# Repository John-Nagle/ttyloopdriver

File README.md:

# ttyloopdriver
Hardware device for driving antique Teletype machines.

For use with 60mA current loop Teletypes at 45 baud.

## Status 

Version 3.3 works, successfully driving a Model 15
Teletype. It's also been built by Steve Garrison and
used to drive a Model 28 Teletype.

# What it is

This is a board to allow connecting antique Teletype machines to a computer through
a USB port. It's for Teletype Model 14 and 15 machines, which use 60mA current
loops.   This board needs no external power supply other than the USB port.
This approach uses only about 1 watt of power, drawing 200mA from the USB port. 

# How it works

The Teletype needs a current of 60mA and an initial voltage of 120V to operate the
selector magnet. The 120V is needed to overcome the huge inductance of the selector
magnet; once the magnet is charged, the required voltage is only a few volts. So the
circuit charges up some capacitors and dumps them into the selector magnet at the start
of each 1 bit (called "MARK" in the Teletype world). After a few milliseconds, a
low-voltage sustain supply takes over to maintain the 60mA current. 

All this is powered entirely from a USB port. So there's a custom switching power
supply.

## Output to the Teletype

At the USB end is a CP2012 breakout board U3.  The Silicon Labs CP2102 is a USB
to serial converter, one of the few which can be reprogrammed for 45 baud
operation.  We reprogram it to map a request for 600 baud to 45 baud.
We also reprogram it to request 400mA from the USB port.

There are two power supplies for the output. One is a custom switching
power supply which, during SPACE, charges up a pair of 1uF ceramic capacitors C1 and C2 to
120V.  There's a board position for a C3 capacitor as well, in parallel with C1 and C2,
but this has not been necessary. These are through-hole components because very large SMT capacitors have capactance
which declines with voltage, which is unacceptable here. They're ceramics for low internal
resistance. 

These caps provide the initial power to pull in the selector magnet,
pushing 60mA through the huge (measured) at 5.5H inductance of the magnet coils.
The other is a 15V supply U8 which provides sustaining current at 60mA
once C2 and C11 have discharged.  Both power supplies feed, through diode D6,
a solid-state relay U4. The relay is controlled by the transmit
data line TxD from U3.

The switching power supply is controlled by an LT3750 capacitor charging
controller. This is the right tool for the job, but with pin spacing of 0.5mm,
is hard to solder. The LT3750 uses comparators and flip-flops to control
charging. 

The switcher is an isolated boost supply, consisting of
U1, T1, C1, C2, and some passives.  The controller signal GATE
turns the FET in Q1 on and off. Turning Q1 off produces an inductive
kick in T1, which has a 1:10 turns ratio.  This can produce
over 120VDC, which is used to charge C1 and C2.

Charging occurs only during SPACE. During MARK, TxD goes high,
inverter U9 inverts that signal, and so, on a MARK to SPACE
transition, the CHARGE input of U1 sees an edge which starts the
charging process.

When the charging process starts, a flip-flop inside U1 turns
on, and this turns on the GATE signal to Q1. This allows current
to flow through T1. The current ramps up linearly as the inductor
charges. Resistor R3, which is only 0.091 ohm, is used as a current
sense resistor to tell U1 when to shut off GATE, stopping current
though the transformer primary.  The value of R3 controls the maximum
current the charger will draw.

Then the transformer, disconnected from power, dumps its magnetic field
into the secondary, charging C1 and C2 through D1. As this happens, the
voltage across the transformer primary drops, and this is sensed via the
RDCM pin of U1. When that voltage difference is near zero, a comparator
in U1 turns the flip-flop back on, turning on GATE and starting the
cycle again. That's the oscillator in this.

There's also circuitry in U1 which senses the peak voltage level to which 
the primary of U1 rises during each charge cycle via RVout. This
is used to stop charging once the desired voltage has been reached.
It takes about 14ms to charge C1 and C2 to 120V, and then the 
charging stops.  The value of R4 controls this goal.
 
The sustain supply U8 is always on, but there is no load on it
during SPACE, because U4 is turned off.  So the two power
supplies take turns drawing
power from the USB port, which keeps the peak current down.

To allow this circuit to support various selector magnet resistances,
there's a linear current regulator at the end, consisting of Q2 and R5.
Q2 is a depletion-mode MOSFET, an unusual component useful for current
regulation over a wide voltage range. This limits the output current to
60mA. When driving a 220 ohm selector, this circuit isn't doing much
current limiting, but when driving a 55 ohm selector, it is. It also
provides short circuit protection, limiting short circuit current to
60mA. (A previous version of the board had a removable jumper for
adjusting the output current, but that was too 1980s. Now it's fully
automatic.)

## Input from the keyboard

On the keyboard side, U6, a very small 5V to 24V DC-DC
converter, produces enough voltage for Teletype keyboard
contacts, which may have oil or dirt on them.  A 5V
logic level is known to be too weak for this.  Another
opto-isolator, U5, isolates the keyboard from the logic
level circuitry.  There's a BREAK button, SW2, so that
a BREAK can be sent even if no keyboard is present.

## Motor control

A standard 5V solid state relay, such as a Crydom CSW2410-10 can 
be plugged into jack J3 for Teletype motor control.  This will
turn on when the USB serial port raises Request to Send and power is on.
The middle green light of D13 will also turn on.
The "Baudotrss" software package supports this function.

## Power management

This board is powered entirely from a USB port.  There are
strict rules about drawing power from a USB port, and most
modern laptop computers have a USB port controller wihich strictly
enforces them.  If a device draws too much current, even for a 
millisecond, the port turns off power, and usually won't
turn back on again until the laptop is turned off.  Devices
must negotiate with the power source for how much power they
want, and the power source can say no.  This happens when the
device is plugged into the USB port, or when the laptop turns
the port on.

USB devices are guaranteed 100mA, but if you want 
more than that, you have to ask. We ask for 400mA, below the 500mA  maximum
for USB versions 1 and 2, by programming a register in the CP2102
USB interface. We also set the speed for the serial port to 45 baud 
when 600 baud is requested. Programming is done with Silicon Labs' Simplicity Studio
program. 

If the host device says yes to the request for 400mA, the
CP2012 turns on /SUSPEND after successful completion of the
power handshake.  Turning off the device in software (as when
the host computer goes to sleep) will turn off /SUSPEND.

U2 is a AP2553W6 power control IC intended for USB ports.  When
/SUSPEND goes high, it turns on and lets power into the rest of
the board.  It also has a built-in power limit, set to 400mA by
resistor R16, which limits the inrush current as C1 charges at power
up.  If turn-on is successful, and SW1 is on, the VPWR line comes
up and everything on the board gets power, including the top
LED of D13. 

With some operating systems, this won't happen until
the USB port is opened by software.  If the computer goes to sleep,
everything will turn off.  Most USB hubs and some "smart" USB
extension cables will reject a request for 500mA, and the
light won't come on. If the light will come on when the USB cable
is directly plugged into a computer, but won't come on when plugged
in through a long cable or hub, that's the reason.

## Circuit protection

R1 and C3 are a filter for the inductive spikes from
the Teletype selector magnet. The back to back 120V Zeners
D10 and D11 protect against the inductive kickback spikes
from the selector magnet.

On the input side, C8, C12, and L3 keep the inductive
kickback from T1 from getting back into the USB power supply.

The AP2553W6 provides overload protection to the USB port.
It first acts as a current limiter, and if the overload continues,
it heats up, detects the overtemp condition, and cuts power.
The CPC1510G solid state relays also provide current limiting,
in case the printer output is shorted. A dead short across the
output will not damage anything. 

On the Teletype side, everything is isolated from ground and from the USB side.

## Test points

- W1 - low-voltage ground
- W2 - low-voltage power (4.5-5V to W1 GND when powered up)
- W3 - Low side of transformer primary. Watch the switcher action here.
- W4 - High side of switcher current sense resistor
- W5 - high-voltage ground
- W6 - high-voltage high side

## Connectors

J1 is the 1/4" Teletype printer jack, supplying 120VDC at 60mA for a Teletype Model
14 or 15.  Only one printer can be driven; there is not enoug power to drive a whole chain
of machines.

J2 is the 1/4" Teletype keyboard jack, supplying power for a Model 14/15 keyboard.
If nothing is plugged in, the jack shorts and the BREAK button still works.

P2 is a connection for a current meter.  A 100mA meter
is suggested. If a meter is not used, this plug must
be jumpered.

J3 is a smalll jack for a solid state relay (5V in) to
turn on the Teletype motor.  Use of this is optional.

## Controls and indicators

SW1 is the main power switch.

SW2 is a BREAK button, interrupting the keyboard circuit.  This works even if no keyboard is present.

D13 is a 3-high set of green LEDs.

 Bottom - Power ON
 
 Middle - Motor ON
 
 Top - Data output
 
## Computer interface

This unit appears to most computers as a serial port. No special driver should be required.
The port should be opened and set to 600 baud to request
45 baud output.  (The CP2102 must be programmed for this, because many systems can't request 45 baud. 600 baud is used
because that speed was never used for any historical devices.)  When power is on,
Data Set Ready will turn on. When power is on and the motor is running, Clear to Send will turn on.
Power management works; if the computer goes to sleep or suspends, the board will turn off.

## Firmware

The USB to serial converter part on the board must be configured to output 45 baud. See the README file in the
"firmware" directory for instructions.  The driving software must request 600 baud to get 45 baud, because 45
baud is no longer a standard baud rate.

## Fabricating the PC board

Standard Gerber and drill files are in "board/fab/fab.zip".  These are known to work with Seeed Studio
in Shentzen, and should work with other board shops.

## Packaging

The board is 75mm x 120mm, and will fit in a Hammond 1455K1202 box. Patterns for cutting the end plates for the box
are in the directory "case".  The Corel Draw files will work with Epilog laser cutters. We use 1/16" black  acrylic.

## Bill of materials

The bill of materials is in "board/ttydriver01.xml", in KiCAD format.  If this file is run through the Python program
in "tools/src/kicadbomtovendor.py", CSV files are generated. From the command line, when in the directory "board", try

    python3 ../tools/src/kicadbomtovendor ttydriver01.xml --split=VENDOR
    
This will generate CSV files for Digikey, Robotshop, and Coilcraft. The Digikey CSV file can be read by most spreadsheet
programs, and can be fed into the Digikey BOM system, which will look up and price all the parts. Various parts may be out
of stock, but every part on that list has been shipped to us from DigiKey at least once. Substitute out of stock resistors
and caps with equivalent parts if needed.

## Assembly hints

### CP2102 board mounting.

Mount the CP2102 board to the main board without sockets using pin headers.  If you mount it with a socket,
the board won't fit in the box. The CP2102 board comes with angled headers soldered on. Those have to be 
removed.  Solder straight 0.10 inch headers soldered into all the connector holes on the CP2102 board.
The CP2102 board comes with the needed header pins.

### Part substitution

The manufacturer isn't critical.  None of the resistors
are doing anything exotic. R3, R5, and R16 are 1% for a reason;
they're all for current sensing.  The others aren't critical and 5% resistors will work.

#### Obsolete parts
As of March 2021, the SiLabs CP2102 USB to serial part is "not recommended for new designs".
The "drop in replacement" CP2012N **will not work.** It will not run at speeds below 300 baud.

From [SiLabs' porting guide](https://www.silabs.com/documents/public/application-notes/an976-cp2102-3-4-9-to-cp2102n-porting-guide.pdf): 
*"Baud Rate Aliasing is a feature that allows a device to use a pre-defined baud rate in place of a baud rate that is requested by the user.
For example, a device using Baud Rate Aliasing can be programmed to use a baud rate of 45 bps whenever 300 bps is requested.
Baud Rate Aliasing is not supported on the CP2102N.
If Baud Rate Aliasing is used in a CP2102/9 design, the CP2102N is incompatible as a replacement."*

It's become difficult to find serial devices that will run at 45 baud.

### Compatibiilty with Teletype model 15 machines with noise suppression capacitors.
Some Model 15 teletypes have an RF noise suppression capacitor across the keyboard.
The capacitor used is large enough to cause typing errors with this board, because the keyboard circuit doesn't draw
enough power to discharge the capacitor. It may be necessary to disconnect the noise suppression option.

### Soldering

This board has been assembled by using solder paste for the surface mount
parts, placing the parts, then reflowing in a reflow oven. It's a straightforward
job by modern SMT standards. This will require SMT skills and tools. 
U1 has 0.5mm pin spacing, which is tight. 

Check for solder bridges, especially between pins of U1. The pads of U1 are laid out so that 
solder bridges tend to occur near the ends of the pins, where you can
get at them with copper braid and a pointed soldering iron tip.

### Initial testing

#### 1. Plug into a computer with a USB port.

No software required yet.  See that the
computer recognizes it as a USB device.

#### 2. Power check

W1 is ground, W2 is Vcc. Should see
4.8V between those two with the power
switch on.  Bottom green light should
turn on. This may not happen unless some
program has the USB port open, which turns
it on.

#### 3. Reprogram CP2102

If you haven't reprogrammed the
SiLabs baord for 45 baud, do so now.

#### 4. Send data

Send data from Baudotrss or Heavy
Metal at 45 baud. Watch the lights on the
serial board blink.  Top green light should
blink.

#### 5. Check high voltage.

W5 is HV ground. W6 is the high side of
the capacitors.  Expect to see 120V there
with no load on the output.  You have to
send some data to get a voltage there,
because the switcher only charges the
cap after a MARK to SPACE transition.
R14 will discharge the caps in a few
seconds, so after power-off it doesn't
retain high voltage. So you need data
to keep high voltage.

#### 6. Check current

With no data being sent but with something
driving the port, hook up a current meter
to the printer jack.  Should register 60mA,
even into a dead short. The current limiter
can handle this. Q2 will heat up, but it's
rated for 150C and it only heats up to 80C or so
driving a dead short for 20 minutes.

#### 7. Connect a Teletype and send data

If all those tests work, you're probably good
to run a Teletype.  Enjoy!

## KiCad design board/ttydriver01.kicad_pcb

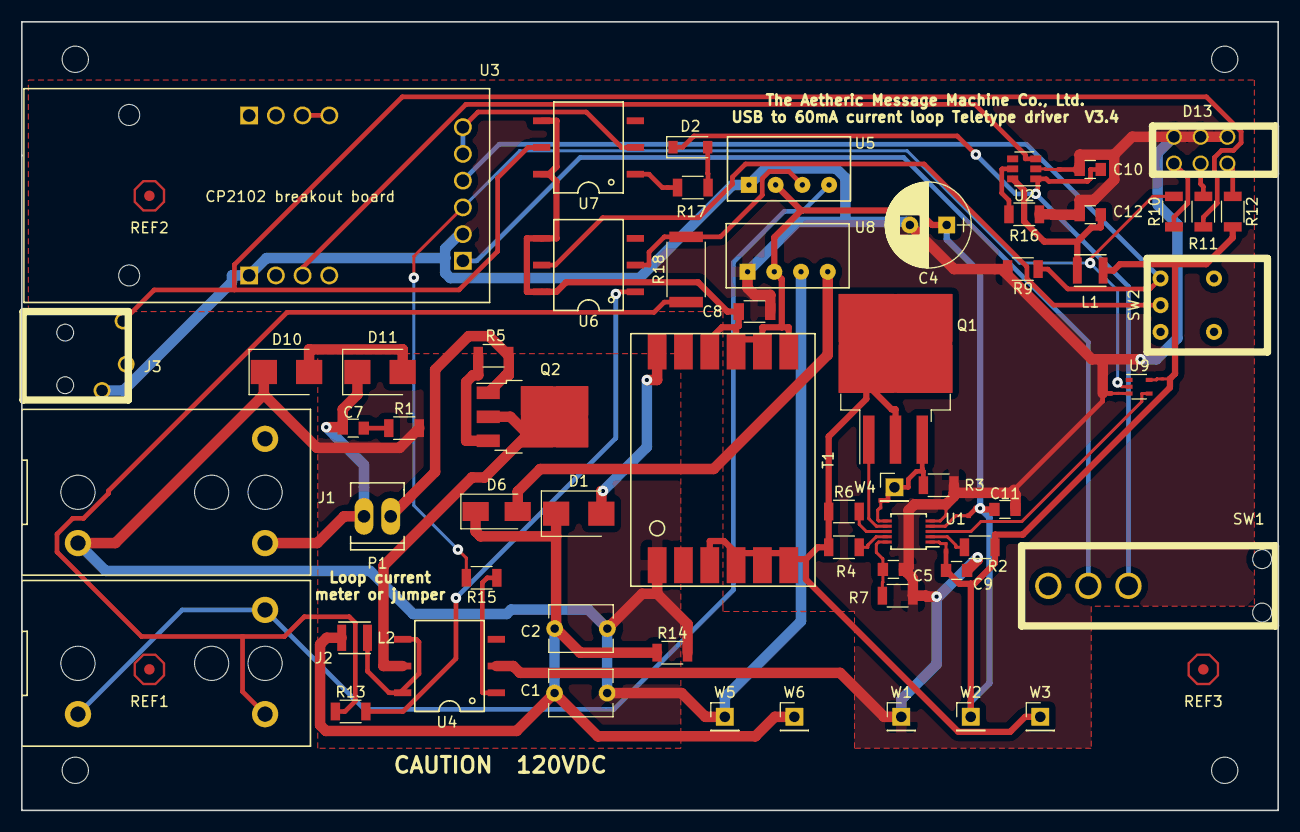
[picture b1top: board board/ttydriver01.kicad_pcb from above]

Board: 2 copper layers, 119.4 x 74.9 mm, 73 parts (0 on the bottom side), 49 nets.

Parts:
C1, C2: 1uf; C_Disc_D6.0mm_W4.4mm_P5.00mm
C4: 220uf; CP_Radial_D8.0mm_P3.50mm
C5: 100pf; C_0805
C7: 1000pf; C_0805
C8: 33uf; C_1206
C9, C11: 10uf; C_0805
C10, C12: 0.1uF; C_0805
D1: D; D_SMB
D2: 1.8V; D_SOD-123
D6: D; SMA_Standard
D10, D11: 120V; SMB_Standard
D13: LED_3; 564-0100
H1, H2, H3, H4: MountingHole_2.5mm
J1, J2: 1/4 in phone jack; Switchcraft-SN37A12A
J3: MOTOR CTL RELAY JACK; MJ-2509N
L1: 6.8uH; Samsung-Inductor-1008
L2: 1uH; Samsung-Inductor-1008
M1, M2, M3, M4, M5, M6, M7: narrower_0.3mm; trace_narrower_0.3mm
P1: CONN_01X02; Socket_MOLEX-KK-RM2-54mm_Lock_2pin_straight
Q1: IRL530NS; TO-263-3_TabPin2
Q2: DN2625; TO-252-3_TabPin2
R1: 10; R_1206
R2: 100K; R_1206
R3: 91m; R_1206
R4: 23K; R_1206
R5: 22; R_1206
R6: 43K; R_1206
R7: 2.49K; R_1206
R9: 1K; R_1206
R10, R11, R12: 390; R_1206
R13: 3.3K; R_1206
R14: 1M; R_1206
R15, R17: 560; R_1206
R16: 53.6K; R_1206
R18: 2.2K; R_2512
REF1, REF2, REF3: Fiducial_Image_Seeed; Fiducial_Image_Seeed_Top
SW1: Switch_SPDT; Toggle-M2012SA2W40
SW2: Button_SPDT; BB15AH-FA
T1: Coilcraft-DA2032; Coilcraft-DA2032-AL
U1: LT3750
U2: AP2553W6; SOT-23-6
U3: CP2102-breakout
U4, U6, U7: CPC1510G; DIP-6_SMD
U5: IE0524S
U8: IE0515S; IE0524S
U9: 74HC1GU04; SOT-353_SC-70-5
W1, W2, W3, W4, W5, W6: TEST_1P; Pin_Header_Straight_1x01_Pitch2.54mm

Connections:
/ENABLE: U2.3, U3.1-3
/HVNEG: C1.2, C2.2, D10.1, J1.S, R1.2, R14.2, T1.1, U8.3, W5.1
/HVPOS: C7.1, D11.1, J1.T, P1.2
/RxD: SW2.2, U6.5
/TxD: R10.2, R15.2, U3.3-3, U9.2
/Vcc: C4.1, C8.1, C9.2, C11.1, L1.2, M2.1, M4.1, M5.1, R2.2, R12.2, T1.7, T1.8, T1.9, T1.10, U5.2, U6.4, U6.6, U7.4, U7.6, U8.2, W2.1
GND: C4.2, C5.2, C8.2, C9.1, C10.2, C11.2, C12.2, D13.1, D13.3, D13.5, J3.S, M1.1, M6.1, M7.1, R3.2, R7.2, R9.2, R16.2, U3.1-1, U3.3-2, U4.2, U5.1, U8.1, W1.1
unnamed: C1.1, C2.1, D1.1, D6.1, L2.2, R14.1, W6.1
unnamed: C5.1, R7.1, U1.10
unnamed: C7.2, R1.1
unnamed: C10.1, D2.1, SW1.1, U2.1
unnamed: C12.1, L1.1, U2.6
unnamed: D1.2, T1.12
unnamed: D2.2, R17.1
unnamed: D6.2, U8.4
unnamed: D10.2, D11.2
unnamed: D13.2, R12.1
unnamed: D13.4, R11.1
unnamed: D13.6, R10.1
unnamed: J2.S, J2.TB, U5.4
unnamed: J2.T, R13.1, R18.1
unnamed: J3.T, R11.2, U7.5
unnamed: L2.1, U4.4, U4.6
unnamed: M1.2, U1.5
unnamed: M2.2, U9.5
unnamed: M3.1, Q1.3, R3.1, W4.1
unnamed: M3.2, U1.6
unnamed: M4.2, U1.1
unnamed: M5.2, U1.4
unnamed: M6.2, U2.2
unnamed: M7.2, U9.3
unnamed: P1.1, Q2.1, R5.1
unnamed: Q1.1, U1.7
unnamed: Q1.2, R4.1, R6.1, T1.3, T1.4, T1.5, T1.6, W3.1
unnamed: Q2.2, U4.5
unnamed: Q2.3, R5.2
unnamed: R2.1, U1.2
unnamed: R4.2, U1.9
unnamed: R6.2, U1.8
unnamed: R9.1, SW2.3, U3.3-4
unnamed: R13.2, U6.1
unnamed: R15.1, U4.1
unnamed: R16.1, U2.5
unnamed: R17.2, U7.1
unnamed: R18.2, U5.3, U6.2
unnamed: SW1.2, U3.3-1
unnamed: U1.3, U9.4
unnamed: U3.2-3, U3.2-4
unnamed: U3.3-5, U3.3-6, U7.2

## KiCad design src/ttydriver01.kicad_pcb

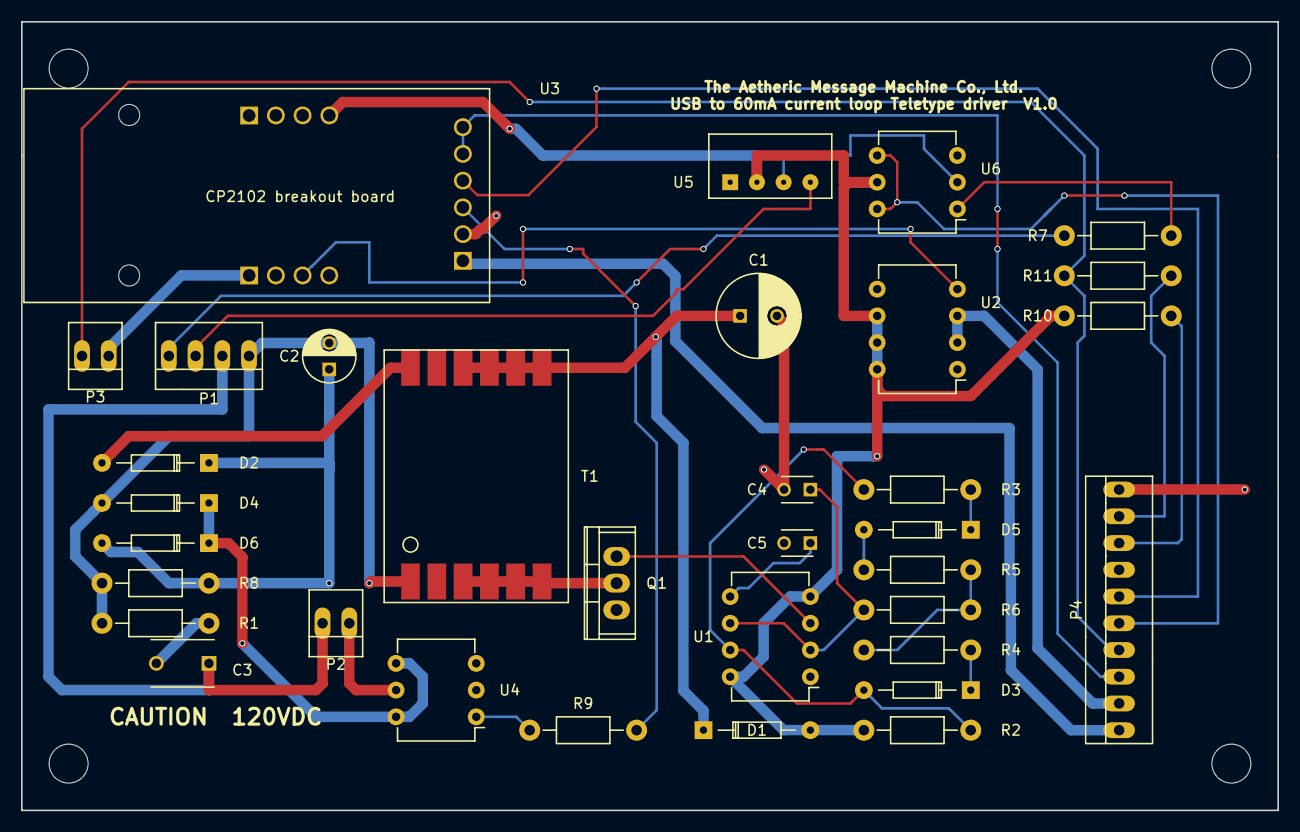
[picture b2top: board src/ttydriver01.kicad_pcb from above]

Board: 2 copper layers, 119.4 x 74.9 mm, 34 parts (0 on the bottom side), 34 nets.

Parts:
C1: 220uf; C_Radial_D8_L11.5_P3.5
C2: 1uf; C_Radial_D5_L6_P2.5
C3: 1000pf; C_Disc_D6_P5
C4: 100pf; C_Disc_D3_P2.5
C5: 0.1uf; C_Disc_D3_P2.5
D1, D2, D6: D; Diode_DO-35_SOD27_Horizontal_RM10
D3, D5: 1N4148; Diode_DO-35_SOD27_Horizontal_RM10
D4: ZENER 120V; Diode_DO-35_SOD27_Horizontal_RM10
P1: CONN_01X04; PINHEAD1-4
P2, P3: CONN_01X02; PINHEAD1-2
P4: CONN_01X10; PINHEAD1-10
Q1: IRLB8721PBF; TO-220-HV
R1: 10; Resistor_Horizontal_RM10mm
R2, R3: 4.7K; Resistor_Horizontal_RM10mm
R4: 22K; Resistor_Horizontal_RM10mm
R5: 68K; Resistor_Horizontal_RM10mm
R6: 2.2K; Resistor_Horizontal_RM10mm
R7: 3.3K; Resistor_Horizontal_RM10mm
R8: 1M; Resistor_Horizontal_RM10mm
R9, R10, R11: 680; Resistor_Horizontal_RM10mm
T1: Coilcraft-DA2032; Coilcraft-DA2032-AL
U1: NE555; DIP-8_W7.62mm
U2: TPS2030P; DIP-8_W7.62mm
U3: CP2102-breakout
U4, U6: G3VM401E; DIP-6_W7.62mm
U5: IE0524S

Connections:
/ENABLE: U2.4, U3.1-3
/HVNEG: C2.2, D4.2, P1.1, R1.2, R8.2, T1.1
/HVPOS: C3.1, P1.2, P2.2
/OSC: Q1.3, U1.3
/RxD: P4.5, U6.4, U6.6
/TxD: R9.2, U3.3-3
GND: C1.2, C4.2, C5.2, P3.1, P4.10, Q1.1, U1.1, U2.1, U3.1-1, U3.3-2, U4.2, U5.1
unnamed: C1.1, D1.1, T1.7, T1.8, T1.9, T1.10
unnamed: C2.1, D2.1, D6.2, R8.1
unnamed: C3.2, R1.1
unnamed: C4.1, R6.2, U1.2, U1.6
unnamed: C5.1, U1.5
unnamed: D2.2, T1.12
unnamed: D3.1, R4.2
unnamed: D3.2, R2.2, R3.1, U1.7
unnamed: D4.1, D6.1, U4.4, U4.6
unnamed: D5.1, R3.2
unnamed: D5.2, R5.1
unnamed: P1.3, U5.4
unnamed: P1.4, R7.1
unnamed: P2.1, U4.5
unnamed: P3.2, P4.4, R11.1
unnamed: P4.1, U3.3-1
unnamed: P4.2, U2.2, U2.3
unnamed: P4.3, U3.3-5, U3.3-6
unnamed: P4.6, U3.3-4
unnamed: P4.8, R10.2
unnamed: P4.9, R11.2
unnamed: Q1.2, T1.3, T1.4, T1.5, T1.6
unnamed: R4.1, R5.2, R6.1
unnamed: R7.2, U6.1
unnamed: R9.1, U4.1
unnamed: U5.3, U6.2
VCC: D1.2, R2.1, R10.1, U1.4, U1.8, U2.6, U2.7, U2.8, U3.2-4, U5.2, U6.5

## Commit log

2016-10-11 Initial explaination
    Basic project info
2016-10-11 Ignore list set properly
2016-10-11 Use only project-local libraries so this will work on Github.
2016-10-12 Moving footprints to project
2016-10-12 Add 24VDC supply for keyboard
2016-10-12 Update README and part number of zener diode
2016-10-12 Added footprint for DC-DC converter
2016-10-12 Moved 3D shapes to .3dshapes file per KiCAD standards
2016-10-15 revise front panel connections. Schematic is about done.
2016-10-16 Improve board layout. Get HV stuff into clear area.
2016-10-16 Everything placed. Ready to start adding tracks
2016-10-16 Connectivity on board doesn't match connectivity on schematic
2016-10-16 Relabled some nets - fixed connectivity
2016-10-16 Add GND fill area. Still no tracks
2016-10-16 New smaller pads for connectors. HV part laid out.
2016-10-17 Ignore _saved_*.sch files.
2016-10-17 All traces in place; now to begin cleanup
2016-10-17 Passes DRC. Valid board. Still needs more cleanup.
2016-10-17 Cleaned up copper fill. Almost ready for fab.
2016-10-17 Adding part number information
2016-10-17 Added all part info except resistors and small caps.
2016-10-18 Working on turning BOM into a usable form for DigiKey
2016-10-18 More progress on BOM converter
2016-10-18 Beginning to generate a BOM on DigiKey. Not all parts listed yet.
2016-10-18 Working on BOM - info valid, but some parts unavailable
2016-10-18 BOM program now produces multiple .CSV files
2016-10-18 Updating BOM to something buyable
2016-10-18 All caps added. Just resistors left to add to BOM
2016-10-18 All parts assigned a vendor
2016-10-18 Change resistor R12 to unused R8
2016-10-18 Closed board
2016-10-19 Ready for fab
2016-10-19 Files ready for fab of board V1.0
2016-10-19 Board ordered from SEEED
2016-10-19 Added front and back mask files
2016-10-19 Add cable harness drawing. No parts list for it yet
2016-10-22 Still adding parts. Need to add indicators and switches
2016-10-24 Parts list as ordered
2016-10-25 Fix schematic symbols not in board library
2016-10-25 Minor cleanup
2016-10-26 Update 3D models to get a good board image
2016-11-15 As-built board image
2016-11-15 Add image to readme
2016-12-06 Doesnt't work. Tell users
2016-12-17 Adding Switchcraft jacks
2016-12-17 Add STLC3085 transformer pad pattern
2016-12-18 Adding new jacks and transformer
2016-12-18 Pads and 3D models for Coilcraft and Switchcraft parts
2016-12-20 Adding 3D models for Coilcraft, Switchcraft, Dialite, and NKK parts
2016-12-20 Add SPICE model
2016-12-21 Better 3D model
2016-12-26 Add LED and jumper for 220 ohm selector magnet
2016-12-30 Add LED, simplify full wave bridge, change OSC INHIBIT resistor
2017-01-02 Revising schematic for V2. Not done.
2017-01-02 Revising schematic for V2. Some DRC errors.
2017-01-02 Close to final design, pending tests
2017-01-04 Basic schematic complete; BOM info and footprints not ready
2017-01-05 Working on adding footprints
2017-01-06 More adding of footprints
2017-01-06 Footprints filled in; initial schematic complete except for all BOM info
2017-01-07 Beginning board layout
2017-01-07 Minor board update
2017-01-08 Initial go at placement on board
2017-01-08 Fix minor placement problems
2017-02-06 Fabbable board, but BOM not entirely filled in
2017-02-06 Fix README
2017-02-07 Move components slightly to improve layout
2017-02-07 Generate fab files. Awaiting proto test before fabbing
2017-02-07 Untested but fabbable board
2017-02-07 Add image of board
2017-03-02 PC board generated good BOM for DigiKey
2017-03-03 Fixed resistor and cap part numbers. Not done.
2017-03-03 Fixed resistor and cap part numbers. As ordered
2017-03-03 Change SPICE sim to match orderable R and C values
2017-03-04 Trying to fix problem with schematic symbol
2017-03-11 Remove 'rescue' library, not needed.
2017-03-11 KiCAD changed names of diode 3D models. Fix accordingly.
2017-03-11 All 3D model links changed to new parts.
2017-03-29 Note some problems on schematic
2017-04-05 Last changes to 2.0 board notes
2017-04-10 Close to working, but some component values may change. Not all part numbers for resistors and caps set.
2017-04-10 Ready for trying autorouting.
2017-04-10 First try at 2.1 autorouting
2017-04-11 Successful autoroute. Board lacks mounting holes
2017-04-11 Successful autoroute. Mounting holes added. Check further before fab.
2017-04-11 BOM data updated. Next, final check before fab
2017-04-11 Generated fab files
2017-04-11 Generated fab files with bigger via rings to pass DRC
2017-04-20 2.1 as built
2017-04-23 Add notes on results with board 2.1
2017-04-23 V2.2 board fixes in
2017-04-23 V2.2 board fixes on PCB
2017-04-24 Reeady to go to fab
2017-04-27 Update README only
2017-05-13 New circuit simulation with 2uf cap. Appears to work in sim.
2017-05-13 Rework for 2uf cap design. Sim works
2017-05-13 Mods for v2.3 complete - ready to try layout
2017-05-13 Successful routing - needs final check
2017-05-13 Moved some parts to reduce trace length
2017-05-13 Update documentation
2017-05-14 Add fidicuial marks
2017-05-14 Add bottom fidicuial footprint
2017-05-14 Use modified fiducial with exposed copper octagon
2017-05-15 Ready to go to fab
2017-05-15 Fab files generated
2017-06-27 Final 2.x version, as built, doesn't output enough power
2017-06-27 Version 3, first draft
2017-06-27 Complete, but needs a real part for inverter U9
2017-06-27 Passes DRC, some footprint problems
2017-06-28 Beginnings of layout. All components present
2017-06-28 Add capcharger sim
2017-06-28 Working on trace widths
2017-06-29 Board passes DRC; Schematic still has an error
2017-06-29 Board passes DRC; corners clipped on layout
2017-06-29 Fix solder mask tolerance to avoid exposed copper at sharp corners
2017-06-30 3D models fixed
2017-06-30 Switch optos to SMD form
2017-06-30 Add new footprint for gull-wing opto
2017-07-03 Adding new footprint for DIP-6_SMD parts
2017-07-03 Unrouted board passes DRC
2017-07-03 Routed, ready for manual cleanup. Needs some part numbers
2017-07-03 Adjusted track widths
2017-07-03 Close to done.
2017-07-04 All 3D models and tracks OK. Just need some part numbers
2017-07-04 Ready for fab and ordering
2017-07-22 Begin v3.1 board.
2017-07-22 Autorouting works
2017-07-28 KiCAD version update?
2017-08-01 Adding more bypass caps to reduce ringing
2017-08-02 Added more bypass caps, changed D1 for faster diode
2017-08-02 New layout with shorter paths in switcher area and a copper pour
2017-08-02 Adjusting copper pour. Layout could use some tweaking but is close
2017-08-02 Update schematic
2017-08-02 Fix D1 3D model
2017-08-04 Routed, but no ground plane
2017-08-04 Routed better. No ground plane, but heavier ground in good place
2017-08-04 Add copper pours
2017-08-04 Generate fabrication files
2017-08-04 As submitted for fab
2017-08-29 Board 3.1 as built and tested
2017-08-30 Beginning 3.2 board
2017-08-30 First routed 3.2 board. No copper pour yet.
2017-08-31 Trying new current limiter simulation.
2017-09-04 Add active current limiter
2017-09-04 Add active current limiter on board. Good autoroute, no fills yet.
2017-09-04 Add active current limiter on board. Good autoroute, fills, almost ready for fab
2017-09-04 Add DN2535 SPICE model
2017-09-04 As sent to fab
2017-09-08 Add .gitattributes because GitHub is mis-identifying KiCAD source
2017-09-08 Fixing file type recognition on Github
2017-09-08 Remove unused device sim file
2017-09-17 Board 3.2 built and tested. Notes.
2017-09-19 Update for current board
2017-09-19 Current image
2017-09-19 Fix 12V->15V
2017-09-21 Update README to fix some minor errors.
2017-09-21 Begin 3.3 board. Fix motor control to use 3.3V into relay, not 5V. Add ferrite bead. Delete unused C3
2017-09-21 Fix comments
2017-09-21 V3.3 board routed
2017-09-22 Laid out board 3.3
2017-09-23 V3.3 board as submitted.
2017-09-25 Fixing 3D images on board because KiCAD libraries changed.
2017-10-09 Add case layout
2017-10-13 Board 3.3 as built and working
2017-10-14 Add BOM files in .csv format
2017-10-14 Add firmware
2017-10-17 Fix part numbers for BOM to avoid duplicate entries
2017-10-17 Regenerate BOM .csv files
2017-12-03 Update after first successful build by another
2017-12-04 Update schematic image
2018-05-02 Begin board 3.4 - adding load resistor for keyboard
2018-07-02 Fix indicator docs
2018-09-10 Add schematic
2019-04-13 PEP8
2019-04-13 Convert to .format() strings
2019-04-13 Remove redundant parens
2019-04-13 `exit` is a helper for the interactive shell - `sys.exit` is intended for use in programs. See: https://stackoverflow.com/questions/6501121/difference-between-exit-and-sys-exit-in-python
2019-04-13 Switch to defaultdict instead of key check
2019-04-13 Use context manager to open file
2019-04-13 Use augmented assignments
2019-04-13 Avoid string concatenation
2019-04-13 Fix error when not using splitcol
2019-04-13 remove unused variable
2019-04-13 Use os.path.splitext
2019-04-13 Remove obsolete try/except
2019-04-13 reorder imports
2021-03-27 Update README for 2021
